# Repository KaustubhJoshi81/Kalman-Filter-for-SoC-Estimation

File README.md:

# Kalman-Filter-for-SoC-Estimation
As a part of acedemic curriculum, our project group is working on Active Battery Management System. Our goal with this project is to come up with our own circuit instead of using Monolithic ICs. The system is divided into three parts: SoC estimation, Cell-Balancing and Battery pack Protection. I am working on SoC estimation. 
I have designed a PCB using eagle, which measures the cell-voltage and cell-current and also designed analog accmulator which acts as a coulomb counter. In the future, I want to integrate the analog coulomb counter int the SoC estimation algorithm.
Currently, I am working on the SoC estimation algorithm. The algortihm uses Resistive cell model and Extended Kalman Filter to linearlize the OCV-SoC curve.

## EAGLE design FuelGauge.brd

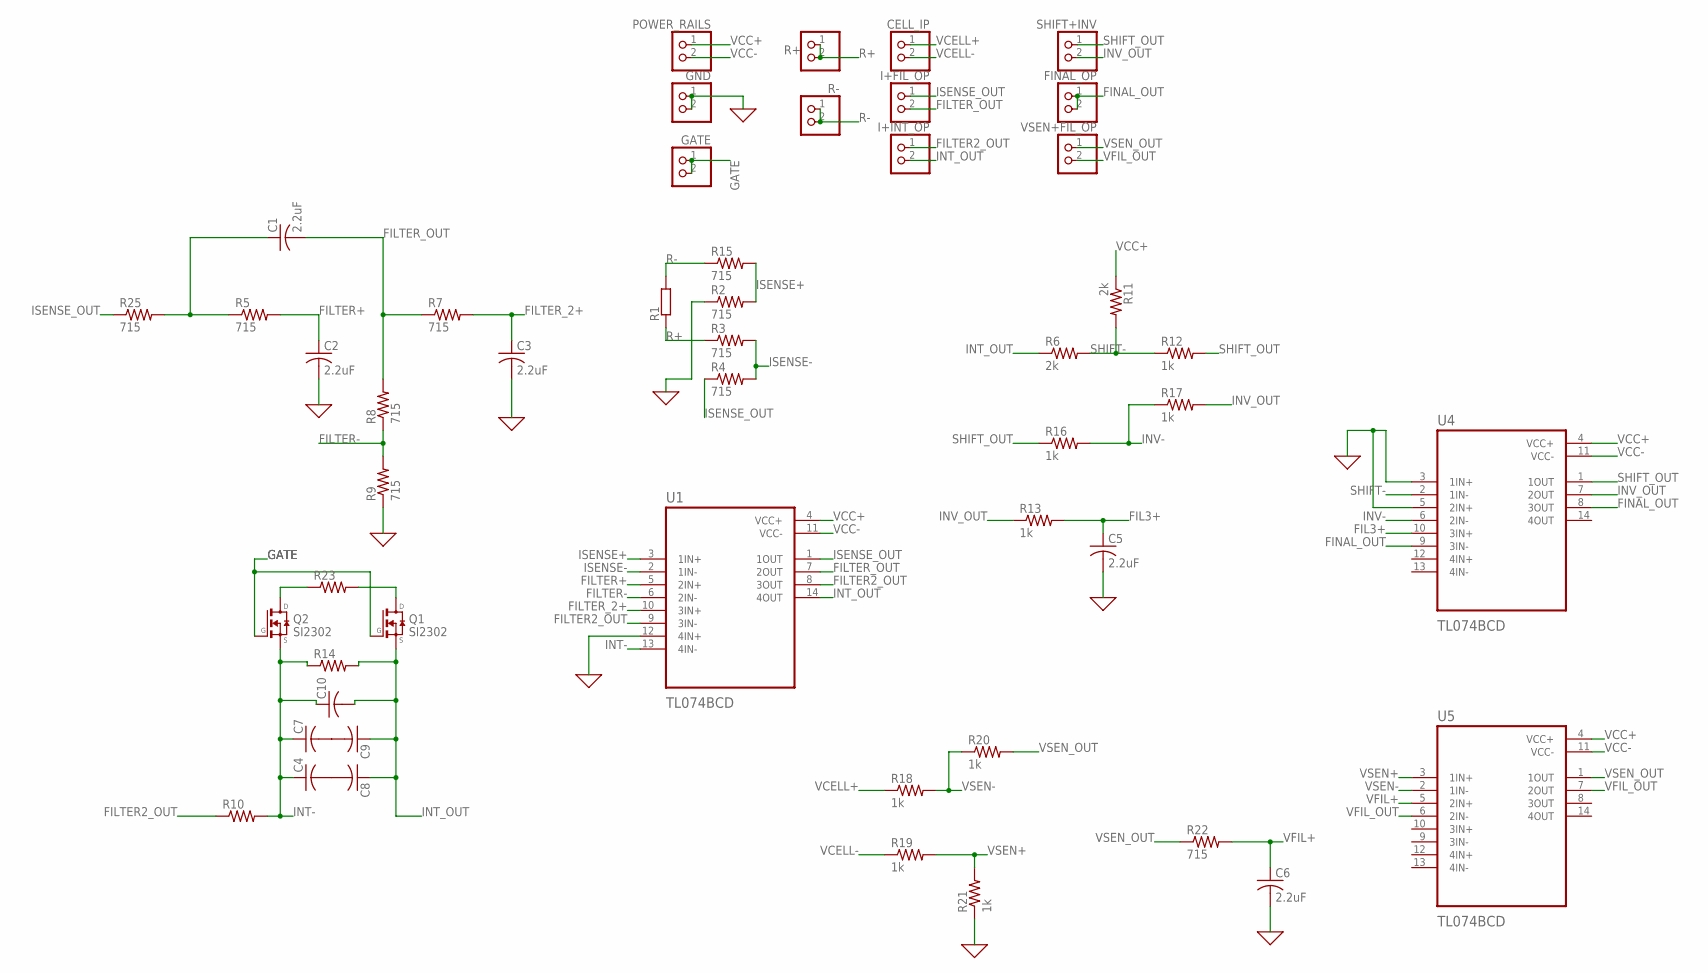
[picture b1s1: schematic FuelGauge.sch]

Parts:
C1, C2, C3, C5, C6: 2.2uF; C0603
C4, C7, C8, C9: C-US025-050X050; C025-050X050
C10: C-USC0603; C0603
CELL_IP: PINHD-1X2; 1X02
FINAL_OP: PINHD-1X2; 1X02
GATE: PINHD-1X2; 1X02
GND: PINHD-1X2; 1X02
I+FIL_OP: PINHD-1X2; 1X02
I+INT_OP: PINHD-1X2; 1X02
POWER_RAILS: PINHD-1X2; 1X02
Q1, Q2: SI2302; SOT23
R1: SMS-0
R2, R3, R4, R5, R7, R8, R9, R15, R22, R25: 715; R0402
R6, R11: 2k; R0402
R10, R14, R23: R-US_R0402; R0402
R12, R13, R16, R17, R18, R19, R20, R21: 1k; R0402
R+: PINHD-1X2; 1X02
R-: PINHD-1X2; 1X02
SHIFT+INV: PINHD-1X2; 1X02
U1, U4, U5: TL074BCD; SOIC127P600X175-14N
VSEN+FIL_OP: PINHD-1X2; 1X02

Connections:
0: C2.2, C3.2, C5.2, C6.2, GND.1, GND.2, R2.1, R9.1, R21.1, U1.12 (4IN+), U4.3 (1IN+), U4.5 (2IN+)
FIL3+: C5.1, R13.2, U4.10 (3IN+)
FILTER2_OUT: I+INT_OP.1, R10.1, U1.8 (3OUT), U1.9 (3IN-)
FILTER+: C2.1, R5.2, U1.5 (2IN+)
FILTER-: R8.1, R9.2, U1.6 (2IN-)
FILTER_2+: C3.1, R7.2, U1.10 (3IN+)
FILTER_OUT: C1.2, I+FIL_OP.2, R7.1, R8.2, U1.7 (2OUT)
FINAL_OUT: FINAL_OP.1, FINAL_OP.2, U4.8 (3OUT), U4.9 (3IN-)
GATE: GATE.1, GATE.2, Q1.1 (G), Q2.1 (G)
INT-: C4.1, C7.1, C10.1, Q2.2 (S), R10.2, R14.1, U1.13 (4IN-)
INT_OUT: I+INT_OP.2, R6.1, U1.14 (4OUT)
INV-: R16.2, R17.1, U4.6 (2IN-)
INV_OUT: R13.1, R17.2, SHIFT+INV.2, U4.7 (2OUT)
ISENSE+: R2.2, R15.2, U1.3 (1IN+)
ISENSE-: R3.2, R4.2, U1.2 (1IN-)
ISENSE_OUT: I+FIL_OP.1, R4.1, R25.1, U1.1 (1OUT)
unnamed: Q1.3 (D), R23.2
unnamed: C4.2, C8.2
unnamed: Q2.3 (D), R23.1
unnamed: C7.2, C9.2
unnamed: C1.1, R5.1, R25.2
unnamed: C8.1, C9.1, C10.2, Q1.2 (S), R14.2
R+: R1.2, R3.1, R+.1, R+.2
R-: R1.1, R15.1, R-.1, R-.2
SHIFT-: R6.2, R11.2, R12.1, U4.2 (1IN-)
SHIFT_OUT: R12.2, R16.1, SHIFT+INV.1, U4.1 (1OUT)
VCC+: POWER_RAILS.1, R11.1, U1.4 (VCC+), U4.4 (VCC+), U5.4 (VCC+)
VCC-: POWER_RAILS.2, U1.11 (VCC-), U4.11 (VCC-), U5.11 (VCC-)
VCELL+: CELL_IP.1, R18.1
VCELL-: CELL_IP.2, R19.1
VFIL+: C6.1, R22.2, U5.5 (2IN+)
VFIL_OUT: U5.6 (2IN-), U5.7 (2OUT), VSEN+FIL_OP.2
VSEN+: R19.2, R21.2, U5.3 (1IN+)
VSEN-: R18.2, R20.1, U5.2 (1IN-)
VSEN_OUT: R20.2, R22.1, U5.1 (1OUT), VSEN+FIL_OP.1

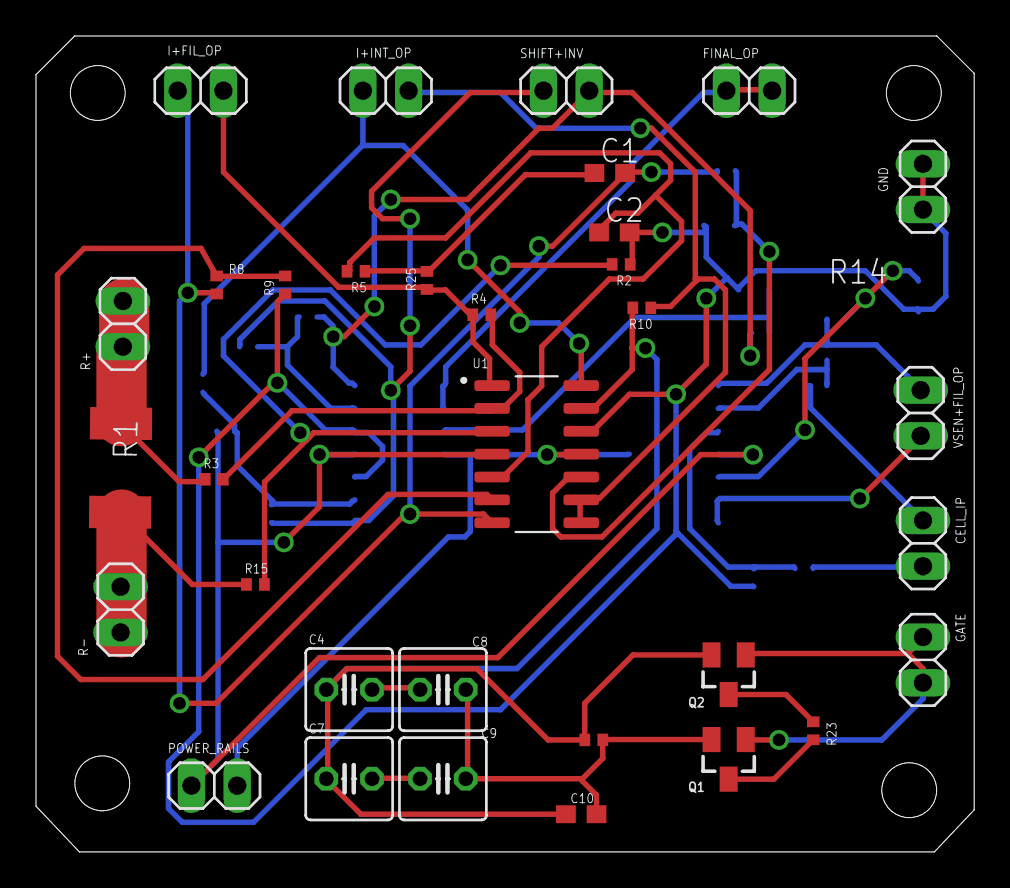
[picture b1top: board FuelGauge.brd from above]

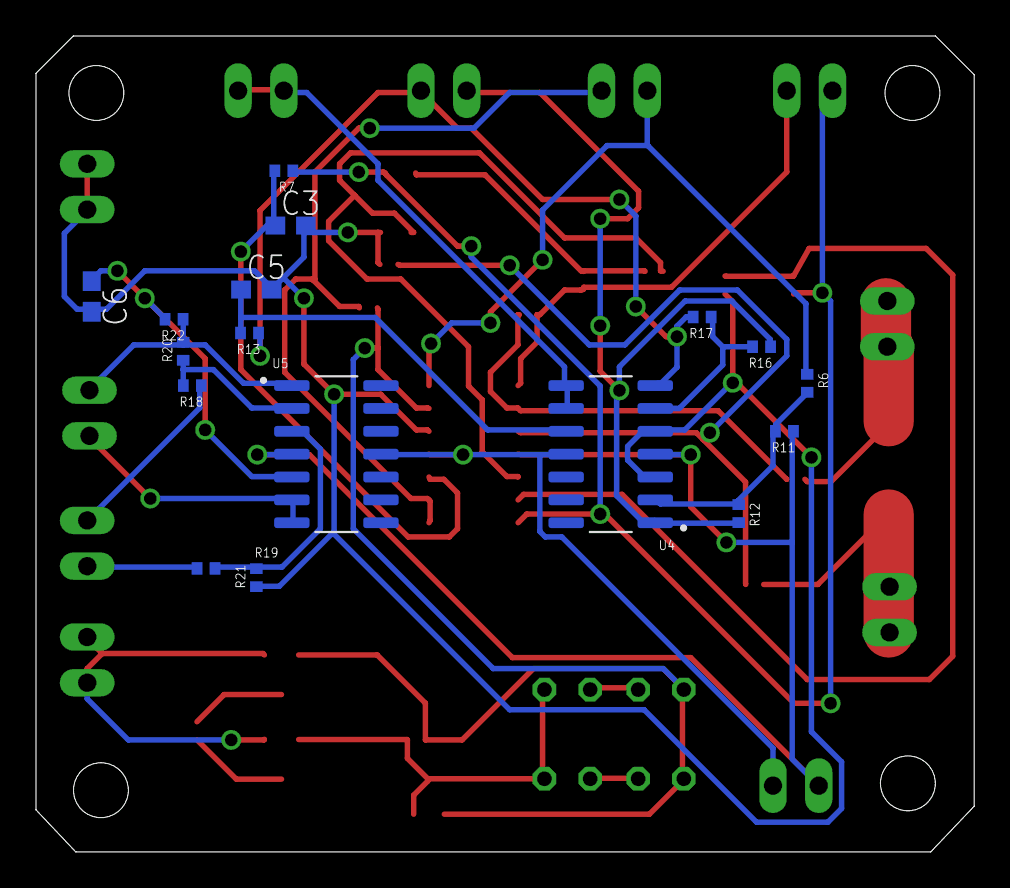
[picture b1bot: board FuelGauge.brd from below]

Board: 2 copper layers, 52.1 x 45.3 mm, 50 parts (17 on the bottom side), 35 nets.
